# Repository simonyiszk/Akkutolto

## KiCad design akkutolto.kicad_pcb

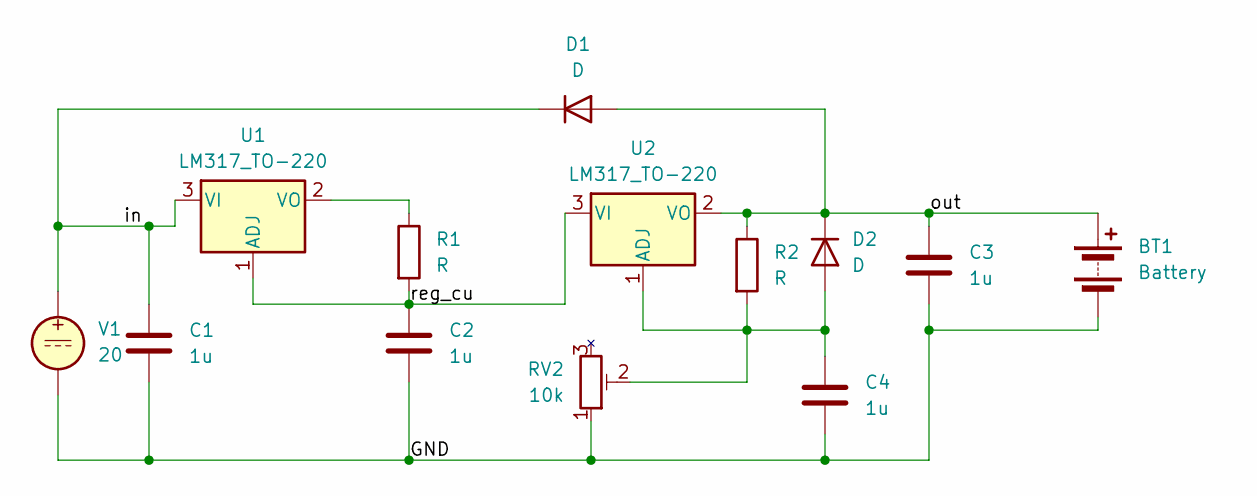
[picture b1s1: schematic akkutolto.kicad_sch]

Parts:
BT1: Battery; AMASS_XT60-M_1x02_P7.20mm_Vertical
C1, C2, C3, C4: 1u; C_0805_2012Metric_Pad1.18x1.45mm_HandSolder
D1, D2: D; D_SOD-323_HandSoldering
R1: R; R_Axial_Power_L25.0mm_W9.0mm_P27.94mm
R2: R; R_0805_2012Metric_Pad1.20x1.40mm_HandSolder
RV2: 10k; Potentiometer_Runtron_RM-065_Vertical
U1, U2: LM317_TO-220; TO-220-3_Horizontal_TabDown
V1: 20; BarrelJack_Wuerth_6941xx301002

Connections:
/GND: BT1.2 (-), C1.2, C2.2, C3.2, C4.2, RV2.1, V1.2
/in: C1.1, D1.1 (K), U1.3 (VI), V1.1
/out: BT1.1 (+), C3.1, D1.2 (A), D2.1 (K), R2.1, U2.2 (VO)
/reg_cu: C2.1, R1.2, U1.1 (ADJ), U2.3 (VI)
unnamed: C4.1, D2.2 (A), R2.2, RV2.2, U2.1 (ADJ)
unnamed: R1.1, U1.2 (VO)

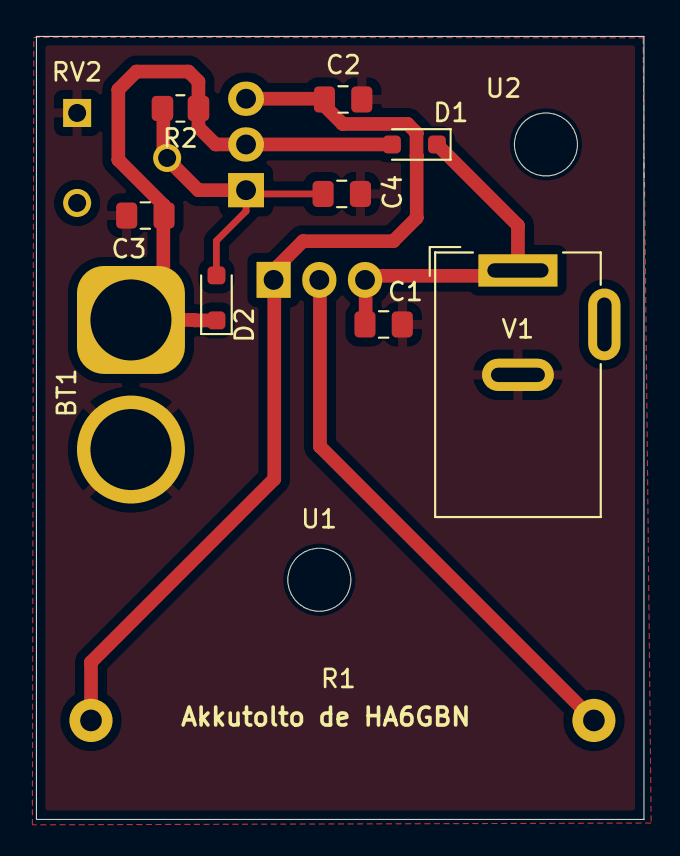
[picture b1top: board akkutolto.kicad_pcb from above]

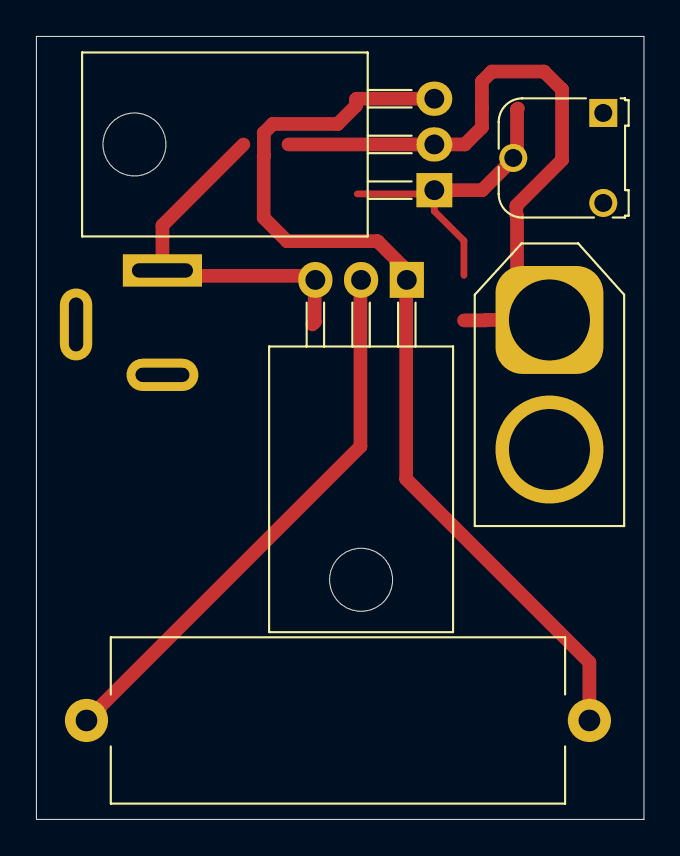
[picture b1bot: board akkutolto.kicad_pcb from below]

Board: 2 copper layers, 33.8 x 43.5 mm, 13 parts (5 on the bottom side), 6 nets.

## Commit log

2025-10-10 LT_added
2025-10-11 LT_updated
2025-10-11 LT_updated2
2025-10-11 Pot_fix
2025-10-11 commit_fix
2025-10-11 Fixed README.md
    Fixed some troubles with readme
2025-10-11 changed stabilizer to LM317
2026-01-15 huzzad Pali
2026-01-15 Huzzad Pali!
2026-01-15 Huzzad Paligit status
2026-01-19 Megvastagítottam pár nagyáramú vezetéket
